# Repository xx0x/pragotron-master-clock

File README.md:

# pragotron-master-clock

USB-C powered master clock source for Pragotron IPJ 0612 and others.

IN PROGRESS

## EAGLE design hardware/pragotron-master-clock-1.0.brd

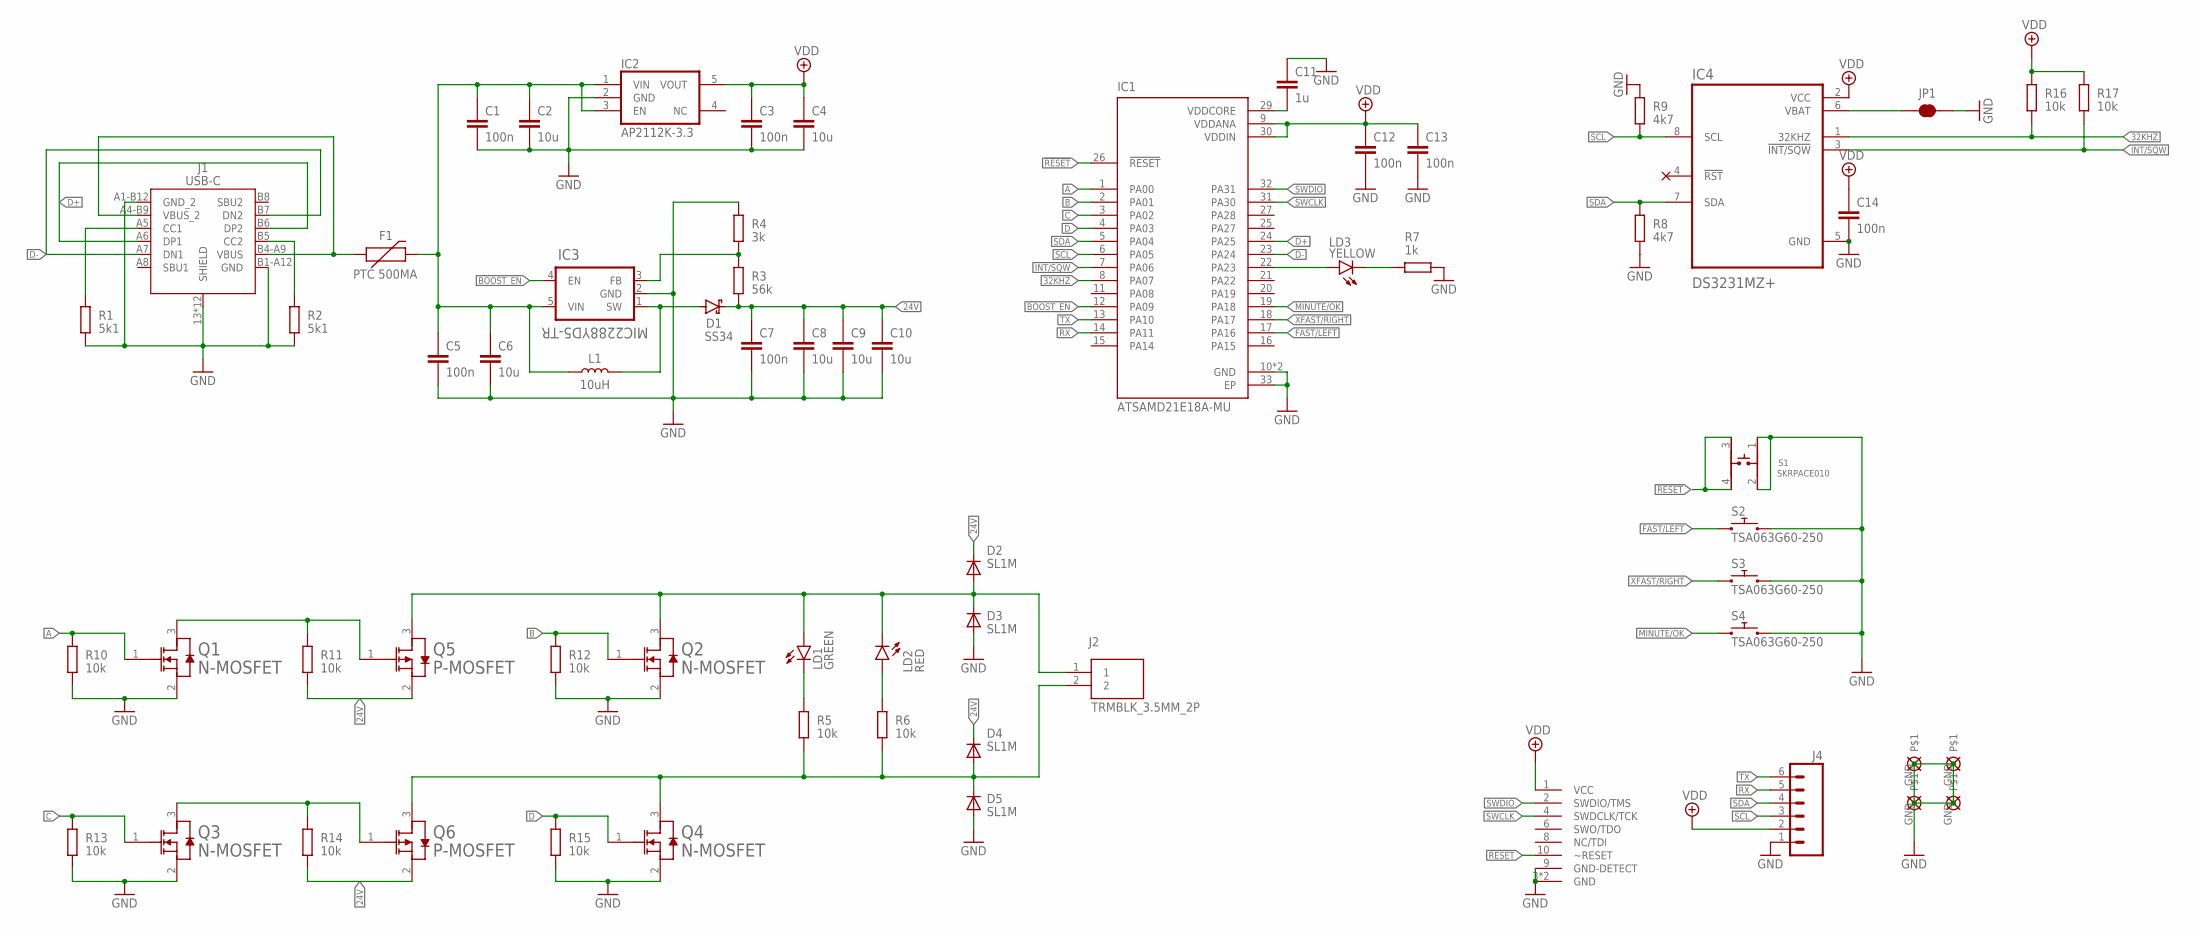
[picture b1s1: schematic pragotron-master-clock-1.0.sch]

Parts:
C1, C3, C5, C7, C12, C13, C14: 100n; CAPACITOR0603
C2, C4, C6, C8, C9, C10: 10u; CAPACITOR0805
C11: 1u; CAPACITOR0603
D1: SS34; SMA
D2, D3, D4, D5: SL1M; SOD123
F1: PTC 500MA; PTC0805
H1, H2, H3, H4: HOLE_3MM_GND_CORNER; 3MM_HOLE_GND_CORNER
IC1: ATSAMD21E18A-MU; QFN50P500X500X100-33N
IC2: AP2112K-3.3; SOT23-5
IC3: MIC2288YD5-TR; SOT23-5
IC4: DS3231MZ+; SO8
J1: USB-C
J2: TRMBLK_3.5MM_2P
J3: 2X5_PITCH_1.27MMTH_NOKEY_UNSHROUDED; CON-CORTEX_2X5_0.05"_TH_NS
J4: M06NO_SILK; 1X06_NO_SILK
JP1: JUMPER-SMT_2_NC_TRACE_NO-SILK; SMT-JUMPER_2_NC_TRACE_NO-SILK
L1: 10uH; ETQP3MXXXKVP
LD1: GREEN; LED_0603
LD2: RED; LED_0603
LD3: YELLOW; LED_0603
Q1, Q2, Q3, Q4: N-MOSFET; SOT23
Q5, Q6: P-MOSFET; SOT23
R1, R2: 5k1; RESISTOR0603
R3: 56k; RESISTOR0603
R4: 3k; RESISTOR0603
R5, R6, R10, R11, R12, R13, R14, R15, R16, R17: 10k; RESISTOR0603
R7: 1k; RESISTOR0603
R8, R9: 4k7; RESISTOR0603
S1: SKRPACE010
S2, S3, S4: TSA063G60-250; TACTILE-SMT-SMALL-PADS

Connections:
24V: C7.1, C8.1, C9.1, C10.1, D1.C, D2.C, D4.C, Q5.2 (SOURCE), Q6.2 (SOURCE), R3.1, R11.1, R14.1
32KHZ: IC1.8 (PA07), IC4.1 (32KHZ), R16.1
!RESET: IC1.26 (!RESET), J3.10 (~RESET), S1.3, S1.4
A: IC1.1 (PA00), Q1.1 (GATE), R10.2
B: IC1.2 (PA01), Q2.1 (GATE), R12.2
BOOST_EN: IC1.12 (PA09), IC3.4 (EN)
C: IC1.3 (PA02), Q3.1 (GATE), R13.2
D: IC1.4 (PA03), Q4.1 (GATE), R15.2
D+: IC1.24 (PA25), J1.A6 (DP1), J1.B6 (DP2)
D-: IC1.23 (PA24), J1.A7 (DN1), J1.B7 (DN2)
FAST/LEFT: IC1.17 (PA16), S2.1, S2.2 (1)
GND: C1.2, C2.2, C3.2, C4.2, C5.2, C6.2, C7.2, C8.2, C9.2, C10.2, C11.1, C12.2, C13.2, C14.2, D3.A, D5.A, H1.GND, H2.GND, H3.GND, H4.GND, IC1.10 (GND), IC1.28 (GND), IC1.33 (EP), IC2.2 (GND), IC3.2 (GND), IC4.5 (GND), J1.13 (SHIELD), J1.14 (SHIELD), J1.15 (SHIELD), J1.16 (SHIELD), J1.A1-B12 (GND_2), J1.B1-A12 (GND), J1.S_1_H1 (SHIELD), J1.S_1_H2 (SHIELD), J1.S_2_H1 (SHIELD), J1.S_2_H2 (SHIELD), J1.S_3_H1 (SHIELD), J1.S_3_H2 (SHIELD), J1.S_4_H1 (SHIELD), J1.S_4_H2 (SHIELD), J3.3 (GND), J3.5 (GND), J3.9 (GND-DETECT), J4.1, JP1.2, Q1.2 (SOURCE), Q2.2 (SOURCE), Q3.2 (SOURCE), Q4.2 (SOURCE), R1.1, R2.1, R4.2, R7.1, R8.1, R9.2, R10.1, R12.1, R13.1, R15.1, S1.1, S1.2, S2.3 (2), S2.4 (2), S3.3 (2), S3.4 (2), S4.3 (2), S4.4 (2)
INT/SQW: IC1.7 (PA06), IC4.3 (!INT/SQW), R17.1
MINUTE/OK: IC1.19 (PA18), S4.1, S4.2 (1)
unnamed: IC3.3 (FB), R3.2, R4.1
unnamed: D1.A, IC3.1 (SW), L1.2
unnamed: F1.2 (1), J1.A4-B9 (VBUS_2), J1.B4-A9 (VBUS)
unnamed: C1.1, C2.1, C5.1, C6.1, F1.3 (2), IC2.1 (VIN), IC2.3 (EN), IC3.5 (VIN), L1.1
unnamed: J1.A5 (CC1), R1.2
unnamed: J1.B5 (CC2), R2.2
unnamed: LD2.A, R6.2
unnamed: C11.2, IC1.29 (VDDCORE)
unnamed: IC1.22 (PA23), LD3.A
unnamed: LD3.K (C), R7.2
unnamed: IC4.6 (VBAT), JP1.1
unnamed: LD1.K (C), R5.2
unnamed: Q1.3 (DRAIN), Q5.1 (GATE), R11.2
unnamed: Q3.3 (DRAIN), Q6.1 (GATE), R14.2
OUT_1: D2.A, D3.C, J2.1, LD1.A, LD2.K (C), Q2.3 (DRAIN), Q5.3 (DRAIN)
OUT_2: D4.A, D5.C, J2.2, Q4.3 (DRAIN), Q6.3 (DRAIN), R5.1, R6.1
RX: IC1.14 (PA11), J4.5
SCL: IC1.6 (PA05), IC4.8 (SCL), J4.3, R9.1
SDA: IC1.5 (PA04), IC4.7 (SDA), J4.4, R8.2
SWCLK: IC1.31 (PA30), J3.4 (SWDCLK/TCK)
SWDIO: IC1.32 (PA31), J3.2 (SWDIO/TMS)
TX: IC1.13 (PA10), J4.6
VDD: C3.1, C4.1, C12.1, C13.1, C14.1, IC1.9 (VDDANA), IC1.30 (VDDIN), IC2.5 (VOUT), IC4.2 (VCC), J3.1 (VCC), J4.2, R16.2, R17.2
XFAST/RIGHT: IC1.18 (PA17), S3.1, S3.2 (1)

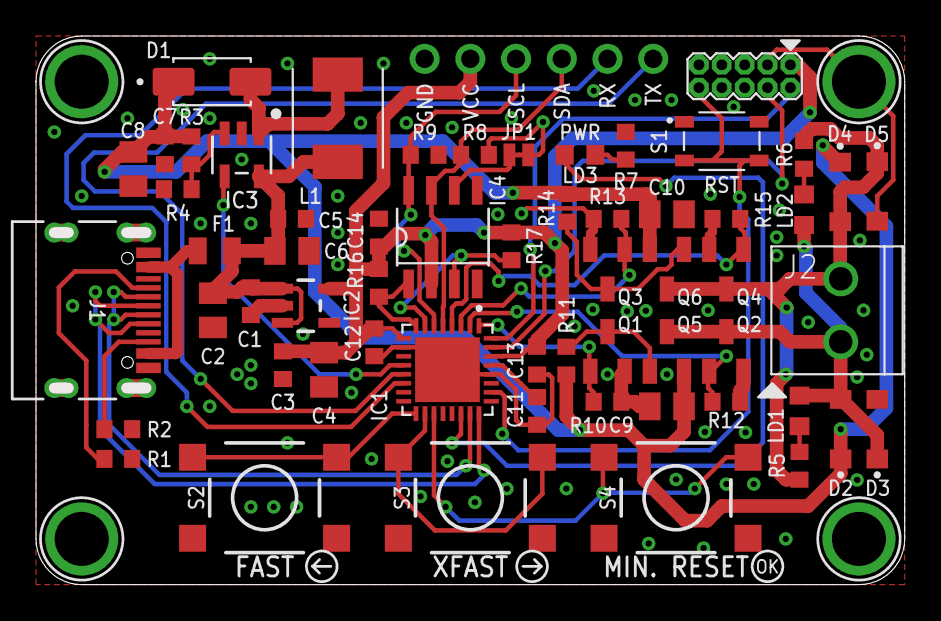
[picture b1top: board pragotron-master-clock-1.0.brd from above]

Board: 2 copper layers, 47.7 x 29.9 mm, 64 parts (0 on the bottom side), 38 nets.

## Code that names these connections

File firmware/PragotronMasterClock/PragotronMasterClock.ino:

/*
 * Pragotron Master Clock
 * - for Pragotron IPJ0612 and others.
 * - based on SAMD21G18A microcontroller and DS3231MZ precise RTC clock
 *
 * Author: Vaclav Mach
 * https://github.com/xx0x/pragotron-master-clock
 * 
 * Sketch uses Adafruit Trinket M0 as the core
 * Modified Trinket M0 bootloader (you can use the Trinket one as well)
 */

#define PBMask(_x) (1 << ((_x)&0x1f))
#define PGrp(_x) ((_x) >> 5)

#define SET_HIGH(n) PORT->Group[PGrp(n)].OUTSET.reg = PBMask(n)
#define SET_LOW(n) PORT->Group[PGrp(n)].OUTCLR.reg = PBMask(n)
#define SET_PIN(n, h) h ? SET_HIGH(n) : SET_LOW(n)
#define TOGGLE_PIN(n) PORT->Group[PGrp(n)].OUTTGL.reg = PBMask(n)
#define SET_OUTPUT(n) PORT->Group[PGrp(n)].DIRSET.reg = PBMask(n)
#define SET_INPUT(n) \
  PORT->Group[PGrp(n)].DIRCLR.reg = PBMask(n); \
  PORT->Group[PGrp(n)].PINCFG[n % 32].reg |= PORT_PINCFG_INEN
#define SET_INPUT_PULLUP(n) \
  SET_INPUT(n); \
  PORT->Group[PGrp(n)].PINCFG[n % 32].reg |= PORT_PINCFG_PULLEN; \
  SET_HIGH(n); \
  PORT->Group[PGrp(n)].PINCFG[n % 32].reg |= PORT_PINCFG_INEN

#define IS_LOW(n) !(PORT->Group[PGrp(n)].IN.reg & (1 << (n % 32)))
#define IS_HIGH(n) !IS_LOW(n)
#define IS_PRESSED(n) IS_LOW(n)


#define PIN_LEDX PIN_PA23

#define PIN_BOOST_ENABLE PIN_PA09
#define PIN_TIMER_INTERRUPT PIN_PA07

#define PIN_OUT_A PIN_PA00
#define PIN_OUT_B PIN_PA01
#define PIN_OUT_C PIN_PA02
#define PIN_OUT_D PIN_PA03

#define PIN_BTN_FAST PIN_PA16
#define PIN_BTN_XFAST PIN_PA17
#define PIN_BTN_MINUTE_RESET PIN_PA18

bool lastState = false;
uint32_t lastTime = 0;

uint32_t clearAt = 0;
uint32_t ledOffAt = 0;

uint16_t secondCounter = 0;
uint8_t minuteCounter = 0;
#define SECOND_COUNT_TO 32768
#define MINUTE_COUNT_TO 60

bool minuteTrigger = false;

enum MODE {
  MODE_NORMAL,
  MODE_FAST,
  MODE_XFAST,
  MODE_COUNT
};

enum BUTTON {
  BUTTON_FAST,
  BUTTON_XFAST,
  BUTTON_MINUTE_RESET,
  BUTTON_COUNT
};

MODE mode = MODE_NORMAL;
bool buttonState[BUTTON_COUNT];
bool prevButtonState[BUTTON_COUNT];
uint8_t buttonsPins[BUTTON_COUNT] = { PIN_BTN_FAST, PIN_BTN_XFAST, PIN_BTN_MINUTE_RESET };

void setup() {
  SET_OUTPUT(PIN_LEDX);
  SET_OUTPUT(PIN_BOOST_ENABLE);
  SET_OUTPUT(PIN_OUT_A);
  SET_OUTPUT(PIN_OUT_B);
  SET_OUTPUT(PIN_OUT_C);
  SET_OUTPUT(PIN_OUT_D);
  SET_INPUT(PIN_PA07);

  for (uint8_t i = 0; i < BUTTON_COUNT; i++) {
    SET_INPUT_PULLUP(buttonsPins[i]);
    buttonState[i] = false;
    prevButtonState[i] = false;
  }

  clear();
  setBoost(false);
  setLed(false);

  // Start precise RTC counter
  attachInterrupt(3, receiveTimeInterrupt, FALLING);  // PA07 is D3 on Trinket
}

void receiveTimeInterrupt() {
  secondCounter = (secondCounter + 1) % SECOND_COUNT_TO;
  if (secondCounter == 0) {
    minuteCounter = (minuteCounter + 1) % MINUTE_COUNT_TO;
    if (minuteCounter == 0) {
      minuteTrigger = true;
    }
  }
}

void clear() {
  SET_LOW(PIN_OUT_A);
  SET_LOW(PIN_OUT_B);
  SET_LOW(PIN_OUT_C);
  SET_LOW(PIN_OUT_D);
}

void setPositive() {
  clear();
  SET_HIGH(PIN_OUT_A);
  SET_HIGH(PIN_OUT_D);
}

void setNegative() {
  clear();
  SET_HIGH(PIN_OUT_B);
  SET_HIGH(PIN_OUT_C);
}

void setLed(bool state) {
  SET_PIN(PIN_LEDX, state);
}

void setBoost(bool state) {
  SET_PIN(PIN_BOOST_ENABLE, state);
}

bool isBoost() {
  return IS_HIGH(PIN_BOOST_ENABLE);
}

void resetCounters() {
  minuteCounter = 0;
  secondCounter = 0;
}

void readButtons() {
  for (uint8_t i = 0; i < BUTTON_COUNT; i++) {
    prevButtonState[i] = buttonState[i];
    buttonState[i] = IS_LOW(buttonsPins[i]);
  }
}

bool justPressed(BUTTON button) {
  return !prevButtonState[button] && buttonState[button];
}

void loop() {
  delay(10);  // debounce

  readButtons();

  if (justPressed(BUTTON_FAST)) {
    if (mode == MODE_FAST) {
      mode = MODE_NORMAL;
      resetCounters();
    } else {
      mode = MODE_FAST;
    }
  }

  if (justPressed(BUTTON_XFAST)) {
    if (mode == MODE_XFAST) {
      mode = MODE_NORMAL;
      resetCounters();
    } else {
      mode = MODE_XFAST;
    }
  }

  if (justPressed(BUTTON_MINUTE_RESET)) {
    mode = MODE_NORMAL;
    resetCounters();
  }

  uint32_t interval = 0;
  uint32_t onLength = 2000;

  switch (mode) {
    case MODE_FAST:
      interval = 1000;
      break;
    case MODE_XFAST:
      interval = 250;
      break;
  }

  if ((mode == MODE_NORMAL && minuteTrigger) || ((mode == MODE_FAST || mode == MODE_XFAST) && (millis() - lastTime >= interval || lastTime > millis()))) {

    if (!isBoost()) {
      setBoost(true);
    }
    if (lastState) {
      setNegative();
    } else {
      setPositive();
    }
    minuteTrigger = false;
    lastTime = millis();
    clearAt = (lastTime + onLength);
    ledOffAt = (lastTime + interval / 2);
    setLed(true);
    lastState = !lastState;
  }

  if (ledOffAt && millis() > ledOffAt) {
    setLed(false);
    ledOffAt = 0;
  }
  if (clearAt && millis() > clearAt) {
    clear();
    clearAt = 0;
    if (mode == MODE_NORMAL) {
      setBoost(false);
    }
  }
}

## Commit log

2024-01-06 schematics ready
2024-01-06 board layout
2024-01-06 finish board, add gerber, bom and cpl
2024-01-06 add version info
2024-01-06 replace 22u with 10u caps (there are no 50V caps in 22u)
2024-01-06 small fixes
2024-01-06 update bom and cpl
2024-01-06 update gerber
2024-01-18 add schematic notes, remove old bom/cpl
2024-01-23 add firmware source code
